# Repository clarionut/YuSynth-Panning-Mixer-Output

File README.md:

# YuSynth Panning Mixer/Output
An extensible version of the YuSynth Output mixer &amp; VC-panner, minus the tone control circuitry.

Very early in the construction of my modular synth it became obvious that I was going to need a multi-channel mixer as an output stage. I'd already built a few YuSynth modules, so his [Mixout-VC Panner](https://yusynth.net/Modular/EN/MIXOUT/index.html) seemed like a promising choice especially as I had an old dual VU meter which could be pressed into service.

The original design includes a passive tone control circuit (which I chose to omit) and uses a two-board architecture with the four VC panner circuits on one board and the mixer and output circuitry on another. My synth is in Eurorack format, so I wanted to keep the board sizes as small as possible (which also makes them cheaper!). I decided to use an alternative physical architecture with the mixer output board (board B in my design) as a motherboard, with two 2-channel VC-panner boards (board A) plugged into it using pin headers.

This allows easy extensibility by adding further 2-channel VC-panner boards mounted on their own panels, daisy-chained from a header on the motherboard. I have indeed added an additional pair of inputs since originally building the module. Details of the construction are shown in the [pictures](https://github.com/clarionut/YuSynth-Panning-Mixer-Output/tree/main/Pictures) folder. Note that the two VC-panner boards mounted on the motherboard have the header pins on the front side on one board and the back side on the other to keep the wiring as clean as possible. Most of the pin headers on the motherboard are on the back side of the board. The pictures also show the additional input board and panel.

I replaced the original non-backlit VU meter with one which can be illuminated, and soldered a 2 pin header to the back of the main power input connection with flying leads to the resistor/LED positioned behind the meter.

The [schematic](https://github.com/clarionut/YuSynth-Panning-Mixer-Output/tree/main/Schematic) folder contains PDFs of the schematic and layout for the VC-panner boards (A) and the motherboard (B). The Kicad projects for these are in their own individual subfolders.

I've also include the [gerbers](https://github.com/clarionut/YuSynth-Panning-Mixer-Output/tree/main/Gerbers) in case these are of direct use to anyone.

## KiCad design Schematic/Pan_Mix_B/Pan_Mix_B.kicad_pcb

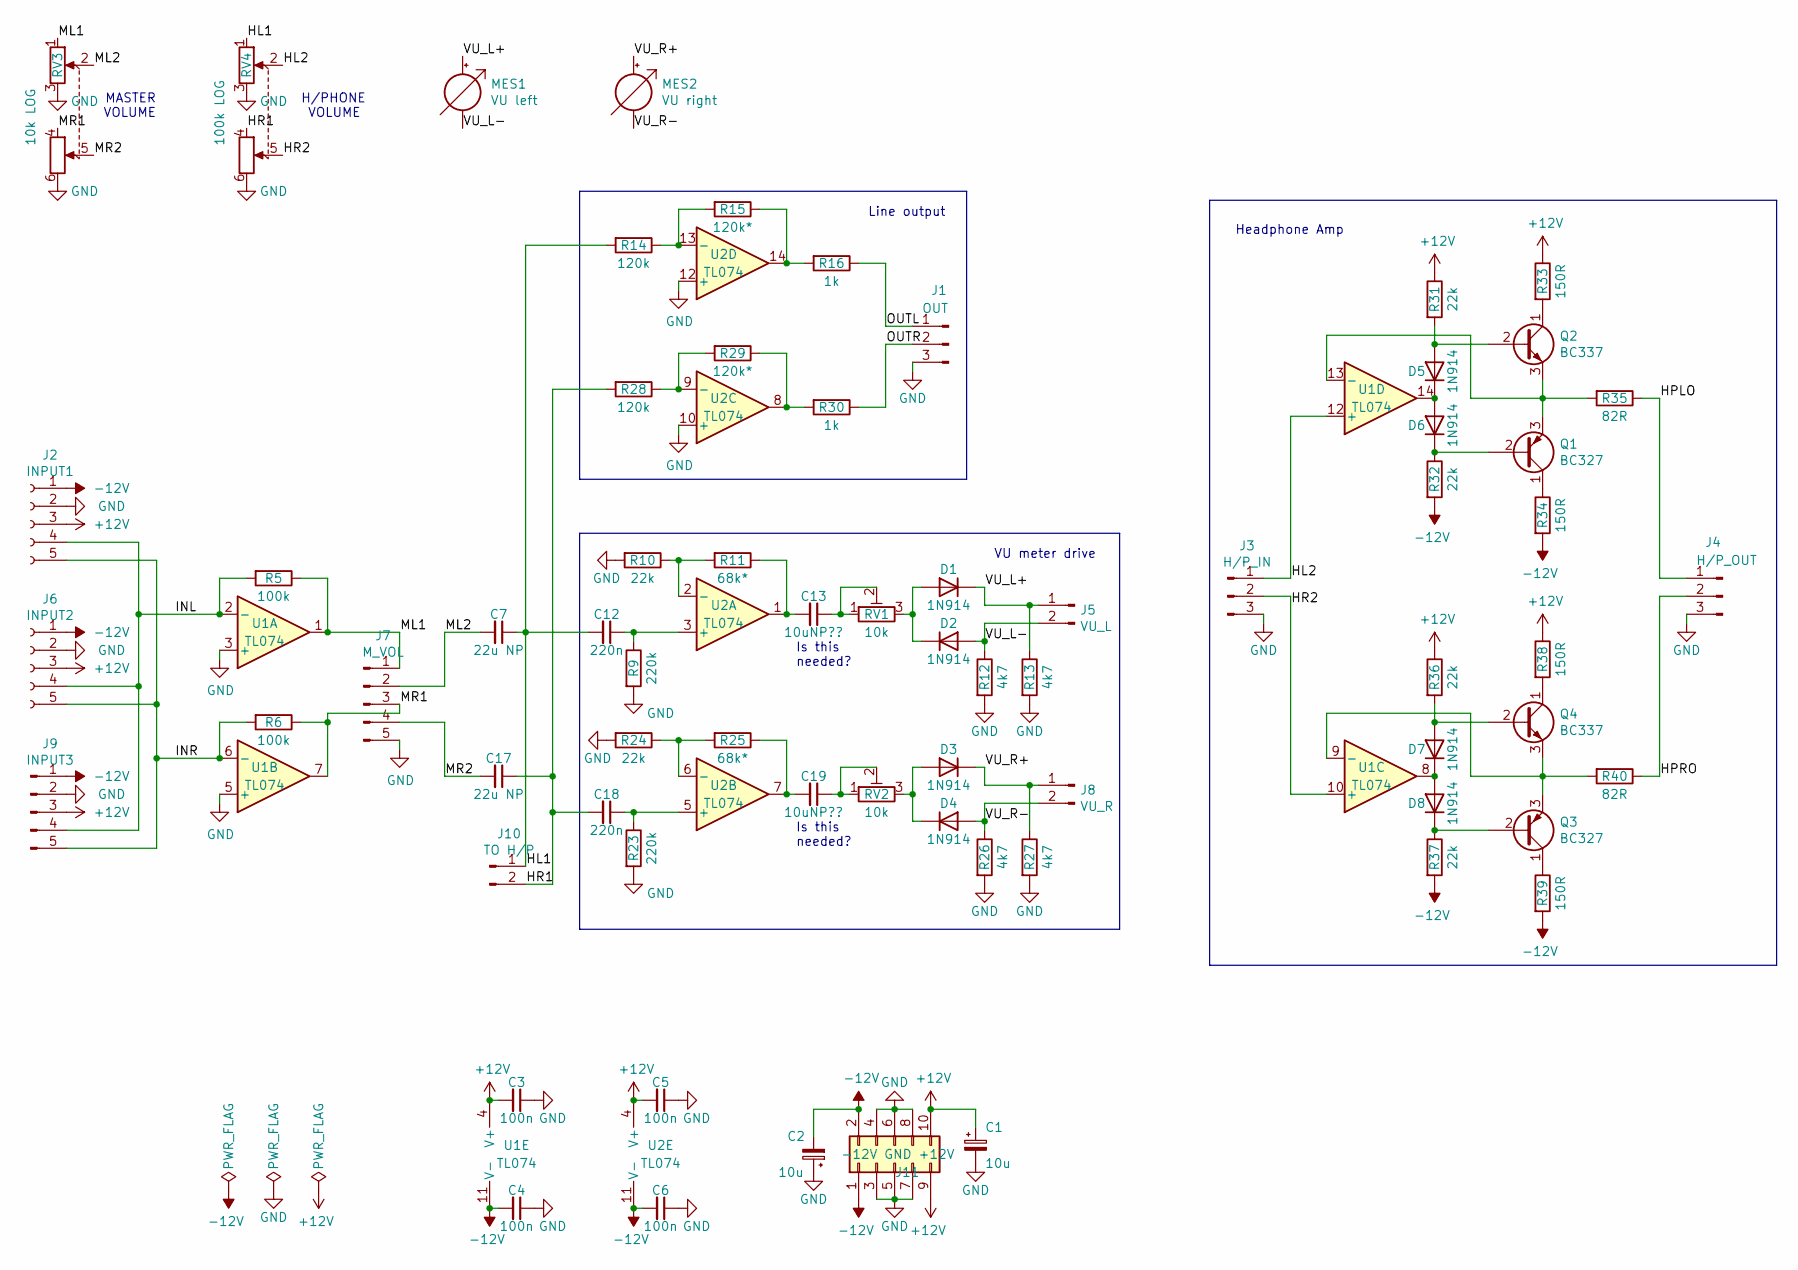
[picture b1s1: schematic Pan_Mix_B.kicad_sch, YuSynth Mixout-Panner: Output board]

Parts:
C1, C2: 10u; CP_Radial_D6.3mm_P2.50mm
C3, C4, C5, C6: 100n; C_Disc_D6.0mm_W2.5mm_P5.00mm
C7, C17: 22u NP; CP_Radial_D7.5mm_P2.50mm
C12, C18: 220n; C_Rect_L7.0mm_W3.5mm_P5.00mm
C13, C19: 10uNP??; CP_Radial_D6.3mm_P2.50mm
D1, D2, D3, D4, D5, D6, D7, D8: 1N914; D_DO-35_SOD27_P7.62mm_Horizontal
J1: OUT; PinHeader_1x03_P2.54mm_Vertical
J2: INPUT1; PinSocket_1x05_P2.54mm_Vertical
J3: H/P_IN; PinHeader_1x03_P2.54mm_Vertical
J4: H/P_OUT; PinHeader_1x03_P2.54mm_Vertical
J5: VU_L; PinHeader_1x02_P2.54mm_Vertical
J6: INPUT2; PinSocket_1x05_P2.54mm_Vertical
J7: M_VOL; PinHeader_1x05_P2.54mm_Vertical
J8: VU_R; PinHeader_1x02_P2.54mm_Vertical
J9: INPUT3; PinHeader_1x05_P2.54mm_Vertical
J10: TO H/P; PinHeader_1x02_P2.54mm_Vertical
J11: -12V GND +12V; PinHeader_2x05_P2.54mm_Vertical
MES1: VU left; L_Axial_L9.5mm_D4.0mm_P2.54mm_Vertical_Fastron_SMCC
MES2: VU right; L_Axial_L9.5mm_D4.0mm_P2.54mm_Vertical_Fastron_SMCC
Q1, Q3: BC327; TO-92_HandSolder
Q2, Q4: BC337; TO-92_HandSolder
R5, R6: 100k; R_Axial_DIN0207_L6.3mm_D2.5mm_P7.62mm_Horizontal
R9, R23: 220k; R_Axial_DIN0207_L6.3mm_D2.5mm_P7.62mm_Horizontal
R10, R24, R31, R32, R36, R37: 22k; R_Axial_DIN0207_L6.3mm_D2.5mm_P7.62mm_Horizontal
R11, R25: 68k*; R_Axial_DIN0207_L6.3mm_D2.5mm_P7.62mm_Horizontal
R12, R13, R26, R27: 4k7; R_Axial_DIN0207_L6.3mm_D2.5mm_P7.62mm_Horizontal
R14, R28: 120k; R_Axial_DIN0207_L6.3mm_D2.5mm_P7.62mm_Horizontal
R15, R29: 120k*; R_Axial_DIN0207_L6.3mm_D2.5mm_P7.62mm_Horizontal
R16, R30: 1k; R_Axial_DIN0207_L6.3mm_D2.5mm_P7.62mm_Horizontal
R33, R34, R38, R39: 150R; R_Axial_DIN0207_L6.3mm_D2.5mm_P7.62mm_Horizontal
R35, R40: 82R; R_Axial_DIN0207_L6.3mm_D2.5mm_P7.62mm_Horizontal
RV1, RV2: 10k; Potentiometer_Bourns_3296W_Vertical
RV3: 10k LOG; Potentiometer_ACP_CA6-H2,5_Horizontal
RV4: 100k LOG; Potentiometer_ACP_CA6-H2,5_Horizontal
U1, U2: TL074; DIP-14_W7.62mm_Socket

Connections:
+12V: C1.1, C3.2, C5.2, J2.3, J6.3, J9.3, J11.9, J11.10, R31.1, R33.1, R36.1, R38.1, U1.4 (V+), U2.4 (V+)
-12V: C2.2, C4.2, C6.2, J2.1, J6.1, J9.1, J11.1, J11.2, R32.2, R34.2, R37.2, R39.2, U1.11 (V-), U2.11 (V-)
/HL1: C7.1, C12.2, J10.1, R14.2, RV4.1
/HL2: J3.1, RV4.2, U1.12 (+)
/HPLO: J4.1, R35.1
/HPRO: J4.2, R40.1
/HR1: C17.1, C18.2, J10.2, R28.2, RV4.4
/HR2: J3.2, RV4.5, U1.10 (+)
/INL: J2.4, J6.4, J9.4, R5.2, U1.2 (-)
/INR: J2.5, J6.5, J9.5, R6.2, U1.6 (-)
/ML1: J7.1, R5.1, RV3.1, U1.1
/ML2: C7.2, J7.2, RV3.2
/MR1: J7.3, R6.1, RV3.4, U1.7
/MR2: C17.2, J7.4, RV3.5
/OUTL: J1.1, R16.1
/OUTR: J1.2, R30.1
/VU_L+: D1.1 (K), J5.1, MES1.2 (+), R13.1
/VU_L-: D2.2 (A), J5.2, MES1.1 (-), R12.1
/VU_R+: D3.1 (K), J8.1, MES2.2 (+), R27.1
/VU_R-: D4.2 (A), J8.2, MES2.1 (-), R26.1
GND: C1.2, C2.1, C3.1, C4.1, C5.1, C6.1, J1.3, J2.2, J3.3, J4.3, J6.2, J7.5, J9.2, J11.3, J11.4, J11.5, J11.6, J11.7, J11.8, R9.2, R10.2, R12.2, R13.2, R23.2, R24.2, R26.2, R27.2, RV3.3, RV3.6, RV4.3, RV4.6, U1.3 (+), U1.5 (+), U2.10 (+), U2.12 (+)
unnamed: C13.1, RV1.1, RV1.2
unnamed: C13.2, R11.1, U2.1
unnamed: C19.1, RV2.1, RV2.2
unnamed: C19.2, R25.1, U2.7
unnamed: D1.2 (A), D2.1 (K), RV1.3
unnamed: D3.2 (A), D4.1 (K), RV2.3
unnamed: D5.2 (A), Q2.2 (B), R31.2
unnamed: D5.1 (K), D6.2 (A), U1.14
unnamed: D6.1 (K), Q1.2 (B), R32.1
unnamed: D7.2 (A), Q4.2 (B), R36.2
unnamed: D7.1 (K), D8.2 (A), U1.8
unnamed: D8.1 (K), Q3.2 (B), R37.1
unnamed: Q1.1 (C), R34.1
unnamed: Q1.3 (E), Q2.3 (E), R35.2, U1.13 (-)
unnamed: Q2.1 (C), R33.2
unnamed: Q3.1 (C), R39.1
unnamed: Q3.3 (E), Q4.3 (E), R40.2, U1.9 (-)
unnamed: Q4.1 (C), R38.2
unnamed: R15.1, R16.2, U2.14
unnamed: R29.1, R30.2, U2.8
unnamed: C12.1, R9.1, U2.3 (+)
unnamed: R10.1, R11.2, U2.2 (-)
unnamed: C18.1, R23.1, U2.5 (+)
unnamed: R24.1, R25.2, U2.6 (-)
unnamed: R28.1, R29.2, U2.9 (-)
unnamed: R14.1, R15.2, U2.13 (-)

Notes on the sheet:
Is this needed?
Line output
VU meter drive
Headphone Amp
H/PHONE VOLUME
MASTER VOLUME

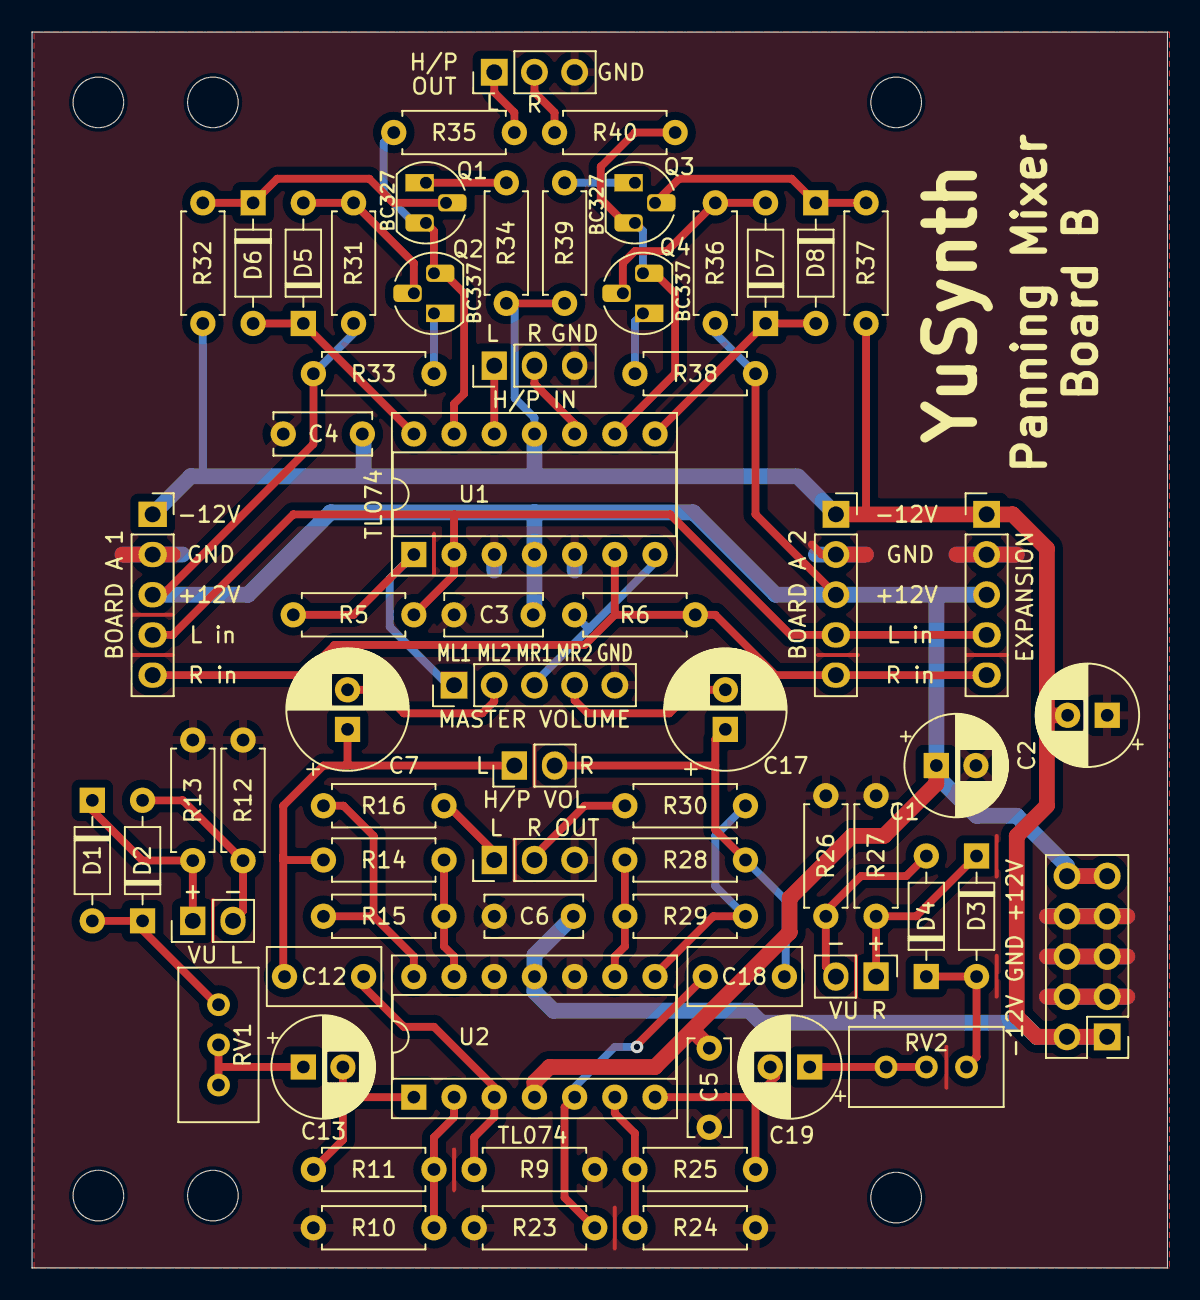
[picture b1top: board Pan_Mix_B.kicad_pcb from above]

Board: 2 copper layers, 71.8 x 78.1 mm, 67 parts (0 on the bottom side), 47 nets.

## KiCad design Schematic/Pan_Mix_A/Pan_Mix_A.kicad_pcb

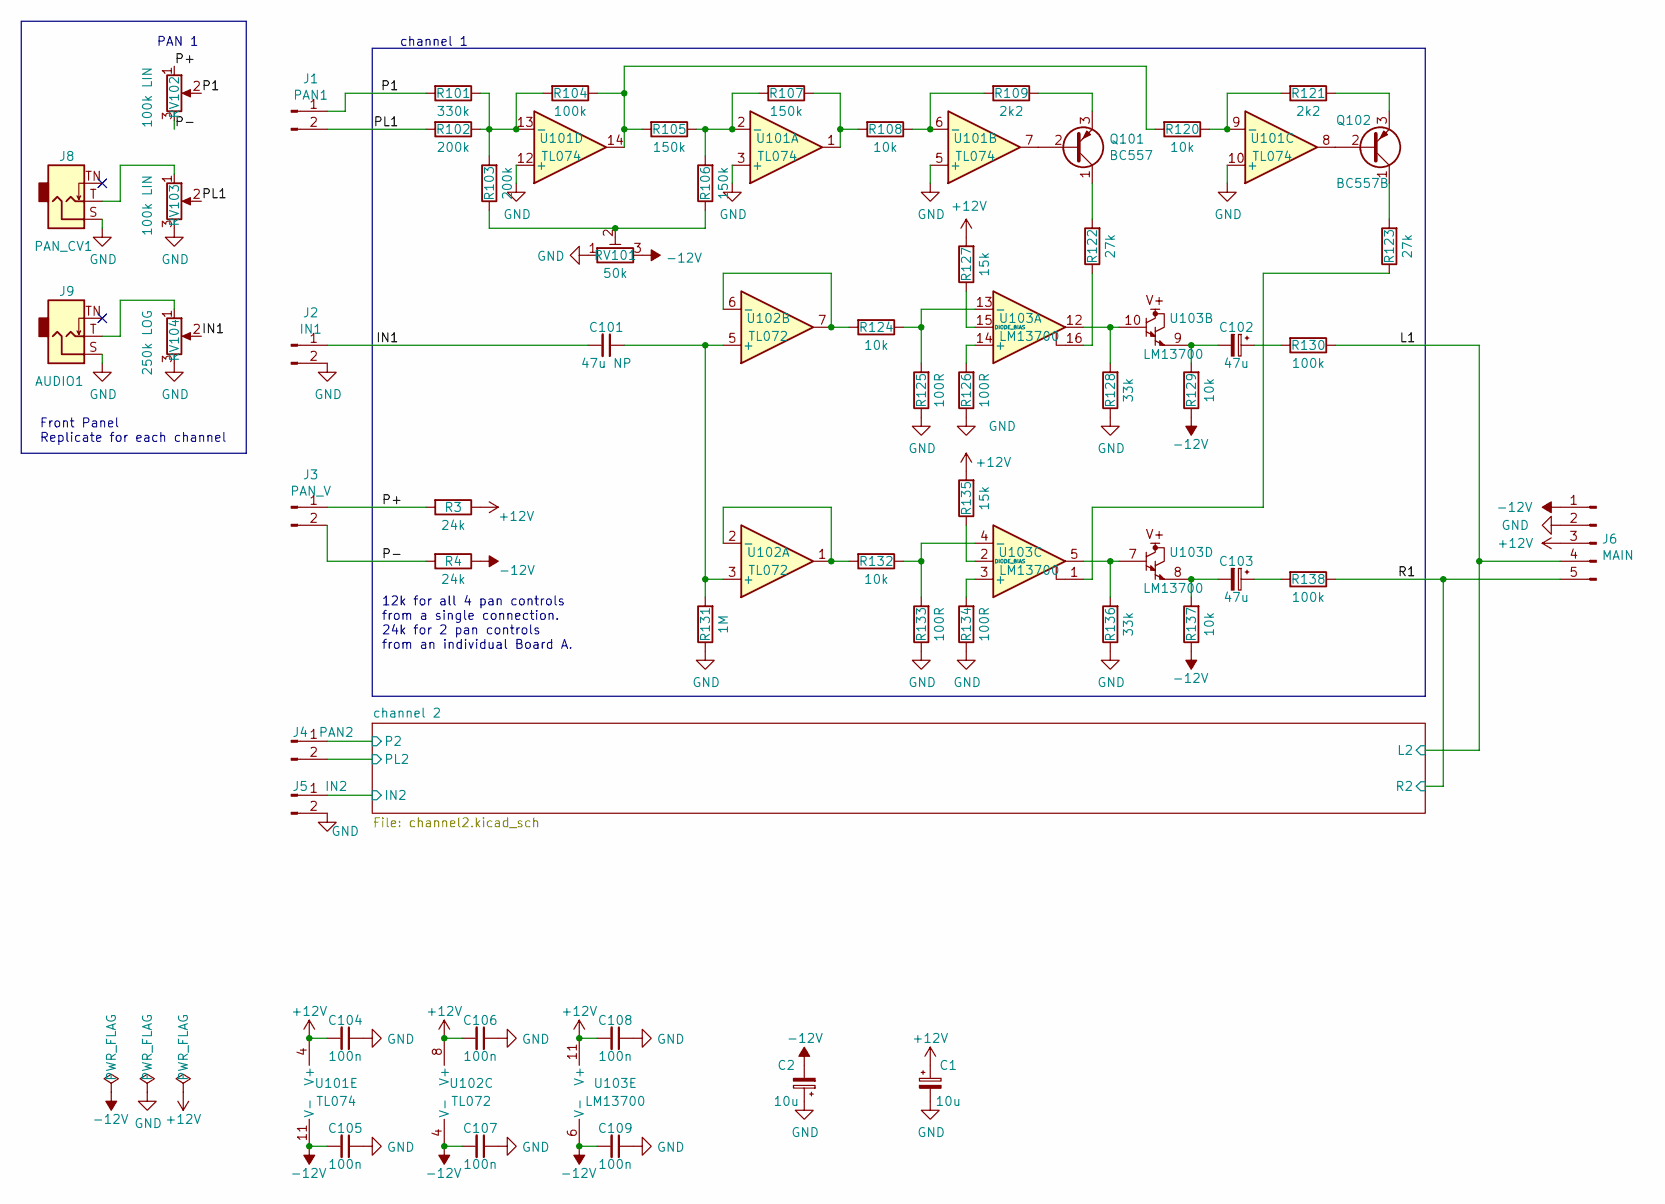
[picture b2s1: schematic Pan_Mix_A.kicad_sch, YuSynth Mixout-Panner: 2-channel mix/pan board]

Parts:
C1, C2: 10u; CP_Radial_D6.3mm_P2.50mm
C101: 47u NP; C_Radial_D6.3mm_H5.0mm_P2.50mm
C102, C103: 47u; CP_Radial_D6.3mm_P2.50mm
C104, C105, C106, C107, C108, C109: 100n; C_Disc_D5.0mm_W2.5mm_P5.00mm
J1: PAN1; PinHeader_1x02_P2.54mm_Vertical
J2: IN1; PinHeader_1x02_P2.54mm_Vertical
J3: PAN_V; PinHeader_1x02_P2.54mm_Vertical
J4: PAN2; PinHeader_1x02_P2.54mm_Vertical
J5: IN2; PinHeader_1x02_P2.54mm_Vertical
J6: MAIN; PinHeader_1x05_P2.54mm_Vertical
J8: PAN_CV1; Jack_3.5mm_CUI_SJ-3524-SMT_Horizontal
J9: AUDIO1; Jack_3.5mm_CUI_SJ-3524-SMT_Horizontal
Q101: BC557; TO-92_HandSolder
Q102: BC557B; TO-92_HandSolder
R3, R4: 24k; R_Axial_DIN0207_L6.3mm_D2.5mm_P7.62mm_Horizontal
R101: 330k; R_Axial_DIN0207_L6.3mm_D2.5mm_P7.62mm_Horizontal
R102, R103: 200k; R_Axial_DIN0207_L6.3mm_D2.5mm_P7.62mm_Horizontal
R104, R130, R138: 100k; R_Axial_DIN0207_L6.3mm_D2.5mm_P7.62mm_Horizontal
R105, R106, R107: 150k; R_Axial_DIN0207_L6.3mm_D2.5mm_P7.62mm_Horizontal
R108, R120, R124, R129, R132, R137: 10k; R_Axial_DIN0207_L6.3mm_D2.5mm_P7.62mm_Horizontal
R109, R121: 2k2; R_Axial_DIN0207_L6.3mm_D2.5mm_P7.62mm_Horizontal
R122, R123: 27k; R_Axial_DIN0207_L6.3mm_D2.5mm_P7.62mm_Horizontal
R125, R126, R133, R134: 100R; R_Axial_DIN0207_L6.3mm_D2.5mm_P7.62mm_Horizontal
R127, R135: 15k; R_Axial_DIN0207_L6.3mm_D2.5mm_P7.62mm_Horizontal
R128, R136: 33k; R_Axial_DIN0207_L6.3mm_D2.5mm_P7.62mm_Horizontal
R131: 1M; R_Axial_DIN0207_L6.3mm_D2.5mm_P7.62mm_Horizontal
RV101: 50k; Potentiometer_Bourns_3296W_Vertical
RV102, RV103: 100k LIN; Potentiometer_ACP_CA6-H2,5_Horizontal
RV104: 250k LOG; Potentiometer_ACP_CA6-H2,5_Horizontal
U101: TL074; DIP-14_W7.62mm_Socket
U102: TL072; DIP-8_W7.62mm_Socket
U103: LM13700; DIP-16_W7.62mm_Socket

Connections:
+12V: C1.1, C104.2, C106.2, C108.2, J6.3, R3.1, R127.2, R135.2, U101.4 (V+), U102.8 (V+), U103.11 (V+); also elsewhere on the board
-12V: C2.2, C105.2, C107.2, C109.2, J6.1, R4.1, R129.1, R137.1, RV101.3, U101.11 (V-), U102.4 (V-), U103.6 (V-); also elsewhere on the board
/IN1: C101.2, J2.1, RV104.2
/L1: J6.4, R130.1; also elsewhere on the board
/P1: J1.1, R101.2, RV102.2
/P+: J3.1, R3.2, RV102.1
/P-: J3.2, R4.2, RV102.3
/PL1: J1.2, R102.2, RV103.2
/R1: J6.5, R138.1; also elsewhere on the board
/channel 2/IN2: J5.1; also elsewhere on the board
/channel 2/P2: J4.1; also elsewhere on the board
/channel 2/PL2: J4.2; also elsewhere on the board
GND: C1.2, C2.1, C104.1, C105.1, C106.1, C107.1, C108.1, C109.1, J2.2, J5.2, J6.2, J8.S, J9.S, R125.1, R126.1, R128.1, R131.1, R133.1, R134.1, R136.1, RV101.1, RV103.3, RV104.3, U101.3 (+), U101.5 (+), U101.10 (+), U101.12 (+); also elsewhere on the board
unnamed: C101.1, R131.2, U102.3 (+), U102.5 (+)
unnamed: C102.1, R130.2
unnamed: C102.2, R129.2, U103.9
unnamed: C103.1, R138.2
unnamed: C103.2, R137.2, U103.8
unnamed: J8.T, RV103.1
unnamed: J9.T, RV104.1
unnamed: Q101.1 (C), R122.2
unnamed: Q101.2 (B), U101.7
unnamed: Q101.3 (E), R109.1
unnamed: Q102.1 (C), R123.2
unnamed: Q102.2 (B), U101.8
unnamed: Q102.3 (E), R121.1
unnamed: R101.1, R102.1, R103.2, R104.2, U101.13 (-)
unnamed: R103.1, R106.1, RV101.2
unnamed: R104.1, R105.2, R120.2, U101.14
unnamed: R105.1, R106.2, R107.2, U101.2 (-)
unnamed: R107.1, R108.2, U101.1
unnamed: R108.1, R109.2, U101.6 (-)
unnamed: R120.1, R121.2, U101.9 (-)
unnamed: R122.1, U103.16
unnamed: R123.1, U103.1
unnamed: R124.1, R125.2, U103.13 (-)
unnamed: R124.2, U102.6 (-), U102.7
unnamed: R126.2, U103.14 (+)
unnamed: R127.1, U103.15 (DIODE_BIAS)
unnamed: R128.2, U103.10, U103.12
unnamed: R132.1, R133.2, U103.4 (-)
unnamed: R132.2, U102.1, U102.2 (-)
unnamed: R134.2, U103.3 (+)
unnamed: R135.1, U103.2 (DIODE_BIAS)
unnamed: R136.2, U103.5, U103.7

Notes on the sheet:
PAN 1
12k for all 4 pan controls from a single connection. 24k for 2 pan controls from an individual Board A.
Front Panel Replicate for each channel
channel 1

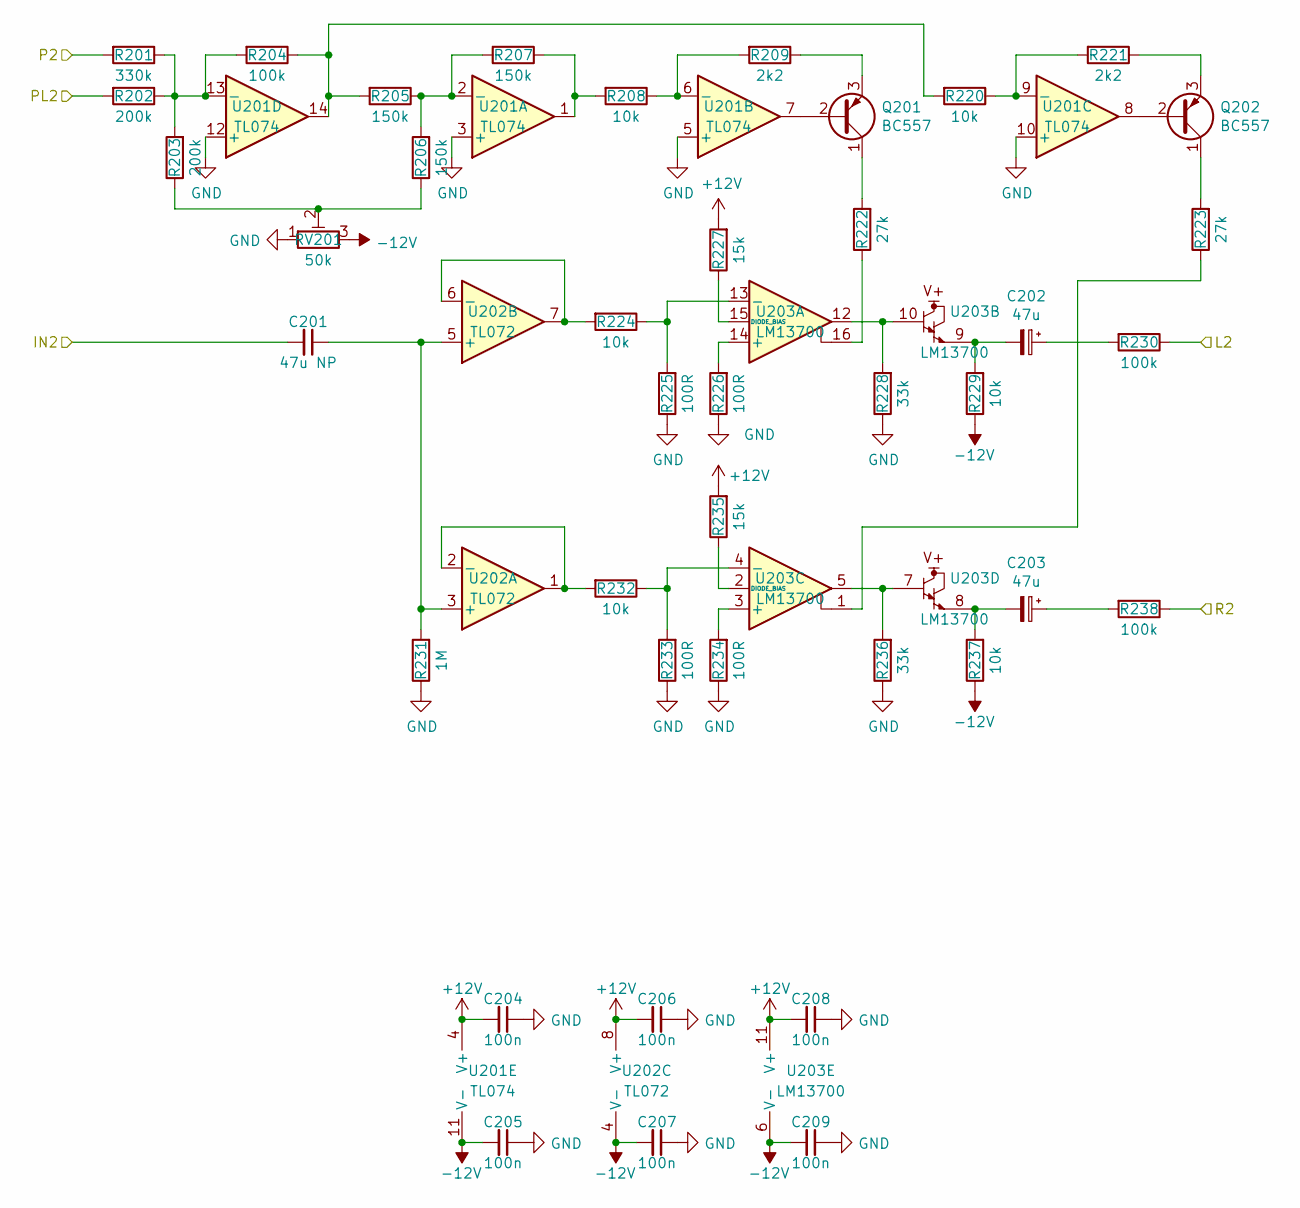
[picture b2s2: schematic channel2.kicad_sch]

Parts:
C201: 47u NP; C_Radial_D6.3mm_H5.0mm_P2.50mm
C202, C203: 47u; CP_Radial_D6.3mm_P2.50mm
C204, C205, C206, C207, C208, C209: 100n; C_Disc_D5.0mm_W2.5mm_P5.00mm
Q201, Q202: BC557; TO-92_HandSolder
R201: 330k; R_Axial_DIN0207_L6.3mm_D2.5mm_P7.62mm_Horizontal
R202, R203: 200k; R_Axial_DIN0207_L6.3mm_D2.5mm_P7.62mm_Horizontal
R204, R230, R238: 100k; R_Axial_DIN0207_L6.3mm_D2.5mm_P7.62mm_Horizontal
R205, R206, R207: 150k; R_Axial_DIN0207_L6.3mm_D2.5mm_P7.62mm_Horizontal
R208, R220, R224, R229, R232, R237: 10k; R_Axial_DIN0207_L6.3mm_D2.5mm_P7.62mm_Horizontal
R209, R221: 2k2; R_Axial_DIN0207_L6.3mm_D2.5mm_P7.62mm_Horizontal
R222, R223: 27k; R_Axial_DIN0207_L6.3mm_D2.5mm_P7.62mm_Horizontal
R225, R226, R233, R234: 100R; R_Axial_DIN0207_L6.3mm_D2.5mm_P7.62mm_Horizontal
R227, R235: 15k; R_Axial_DIN0207_L6.3mm_D2.5mm_P7.62mm_Horizontal
R228, R236: 33k; R_Axial_DIN0207_L6.3mm_D2.5mm_P7.62mm_Horizontal
R231: 1M; R_Axial_DIN0207_L6.3mm_D2.5mm_P7.62mm_Horizontal
RV201: 50k; Potentiometer_Bourns_3296W_Vertical
U201: TL074; DIP-14_W7.62mm_Socket
U202: TL072; DIP-8_W7.62mm_Socket
U203: LM13700; DIP-16_W7.62mm_Socket

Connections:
+12V: C204.2, C206.2, C208.2, R227.2, R235.2, U201.4 (V+), U202.8 (V+), U203.11 (V+); also elsewhere on the board
-12V: C205.2, C207.2, C209.2, R229.1, R237.1, RV201.3, U201.11 (V-), U202.4 (V-), U203.6 (V-); also elsewhere on the board
/L1: R230.1; also elsewhere on the board
/R1: R238.1; also elsewhere on the board
/channel 2/IN2: C201.2; also elsewhere on the board
/channel 2/P2: R201.2; also elsewhere on the board
/channel 2/PL2: R202.2; also elsewhere on the board
GND: C204.1, C205.1, C206.1, C207.1, C208.1, C209.1, R225.1, R226.1, R228.1, R231.1, R233.1, R234.1, R236.1, RV201.1, U201.3 (+), U201.5 (+), U201.10 (+), U201.12 (+); also elsewhere on the board
unnamed: C201.1, R231.2, U202.3 (+), U202.5 (+)
unnamed: C202.1, R230.2
unnamed: C202.2, R229.2, U203.9
unnamed: C203.1, R238.2
unnamed: C203.2, R237.2, U203.8
unnamed: Q201.1 (C), R222.2
unnamed: Q201.2 (B), U201.7
unnamed: Q201.3 (E), R209.1
unnamed: Q202.1 (C), R223.2
unnamed: Q202.2 (B), U201.8
unnamed: Q202.3 (E), R221.1
unnamed: R201.1, R202.1, R203.2, R204.2, U201.13 (-)
unnamed: R203.1, R206.1, RV201.2
unnamed: R204.1, R205.2, R220.2, U201.14
unnamed: R205.1, R206.2, R207.2, U201.2 (-)
unnamed: R207.1, R208.2, U201.1
unnamed: R208.1, R209.2, U201.6 (-)
unnamed: R220.1, R221.2, U201.9 (-)
unnamed: R222.1, U203.16
unnamed: R223.1, U203.1
unnamed: R224.1, R225.2, U203.13 (-)
unnamed: R224.2, U202.6 (-), U202.7
unnamed: R226.2, U203.14 (+)
unnamed: R227.1, U203.15 (DIODE_BIAS)
unnamed: R228.2, U203.10, U203.12
unnamed: R232.1, R233.2, U203.4 (-)
unnamed: R232.2, U202.1, U202.2 (-)
unnamed: R234.2, U203.3 (+)
unnamed: R235.1, U203.2 (DIODE_BIAS)
unnamed: R236.2, U203.5, U203.7

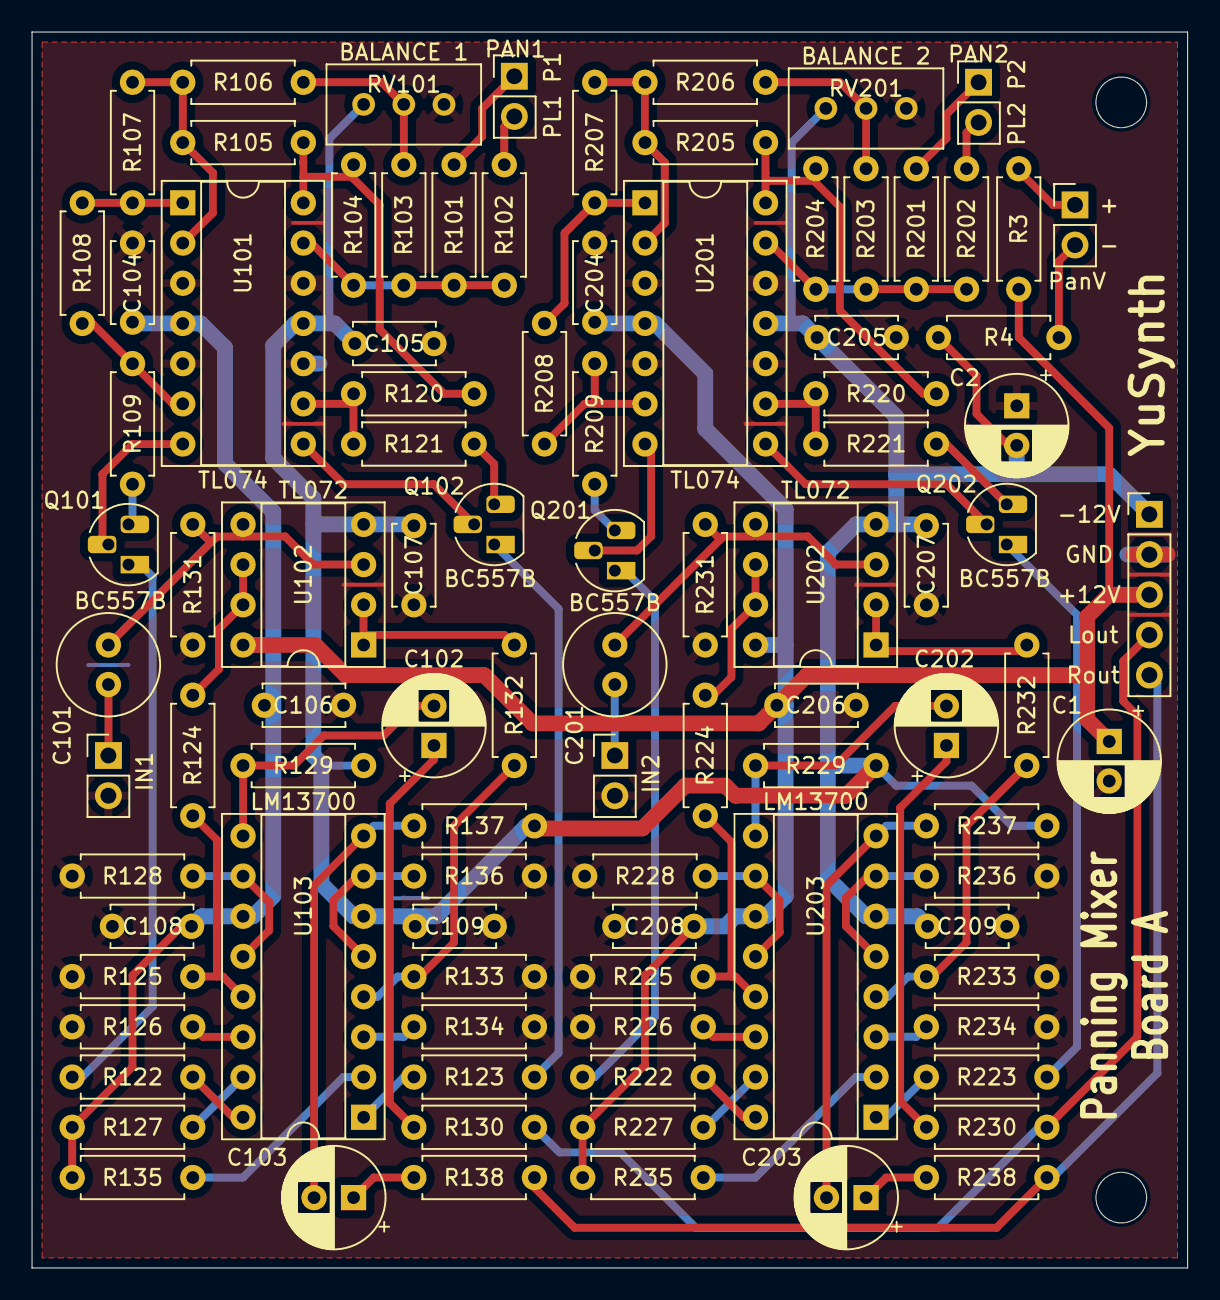
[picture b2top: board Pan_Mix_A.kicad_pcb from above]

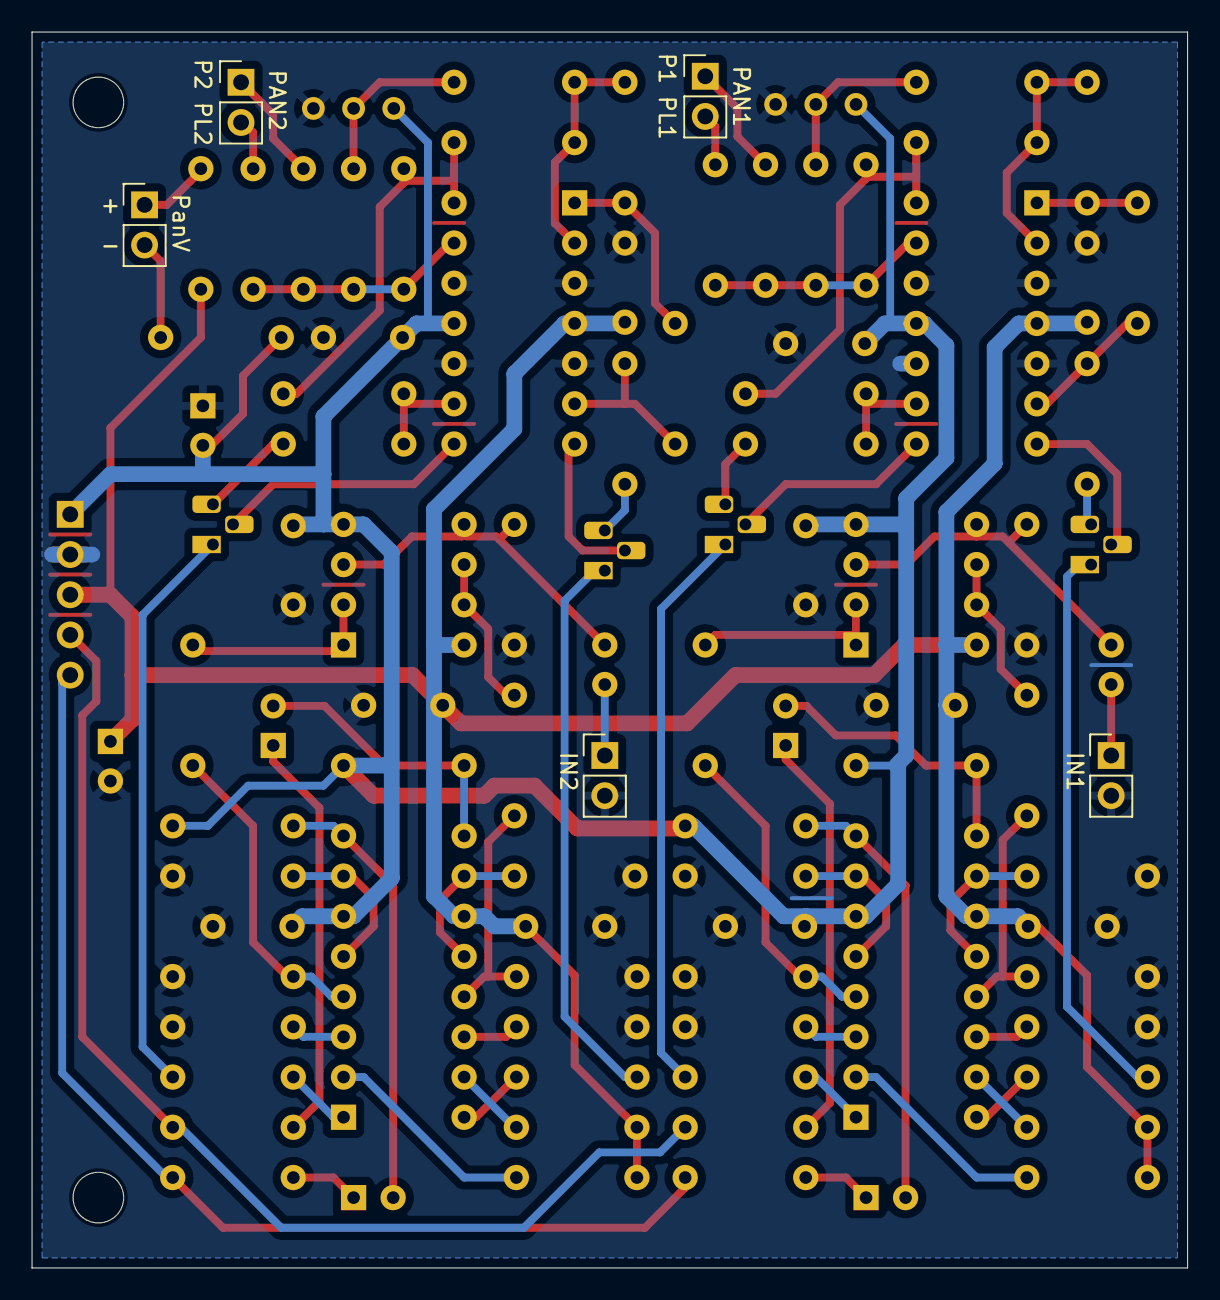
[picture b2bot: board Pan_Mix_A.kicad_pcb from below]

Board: 2 copper layers, 73.0 x 78.1 mm, 96 parts (5 on the bottom side), 73 nets.
